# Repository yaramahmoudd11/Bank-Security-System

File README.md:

# 🏦 Bank Smart Security System

An AI-powered smart security system for banks and restricted areas using embedded systems, machine learning, IoT, cloud services, Docker deployment, and real-time mobile monitoring.

---

## 📸 Project Overview

The **Bank Smart Security System** is designed to automate security monitoring in restricted areas such as bank rooms, storage areas, locker rooms, and sensitive access zones.

The system combines:

* A **Raspberry Pi Linux-based unit** for camera processing, face recognition, server communication, GPIO handling, Docker deployment, and cloud integration.
* A **PIC16F877A microcontroller-based unit** for low-level sensor reading, voltage monitoring, relay control, buzzer control, LED indication, and lock control.
* A **Flutter mobile application** for real-time alerts, door control, voltage visualization, outage statistics, and event review.
* **Supabase** for database, storage, and real-time streams.
* **Firebase Cloud Messaging** for push notifications.
* **HuggingFace** for hosting the trained face-recognition classifier/model files.
* **Docker Hub** for Raspberry Pi deployment.

The system detects unauthorized access, after-hours motion intrusion, and power-fault conditions, then sends real-time alerts to the manager through the mobile application.

---

## 🧠 High-Level System Flow

### Face Recognition Flow

```text
Camera → Face Detection → ArcFace Embedding → SVC Classifier
                                                      |
                                                      v
                                              Known? → Log access
                                              Unknown? → Alert App → User decides action
                                                                          |
                                                                          v
                                                              HTTP request to Pi → Alarm / Lock
```

### Sensor and Power Monitoring Flow

```text
PIR Sensor → PIC16F877A → Close door + Light room → Signal Pi → Capture image → Alert App
Voltage Sensor → PIC16F877A → Power statistics → Raspberry Pi → Alert App
```

---

## ✅ Main Features

* Face recognition access control
* Authorized and unauthorized person classification
* PIR motion detection
* Voltage and power-fault monitoring
* Relay-controlled solenoid lock
* Buzzer and LED alarm indicators
* Raspberry Pi camera evidence capture
* Supabase cloud database integration
* Supabase storage for alert images
* Firebase Cloud Messaging notifications
* Real-time mobile alert streaming
* Remote door lock/unlock control
* Live voltage monitoring and visualization
* Power stability percentage
* Outage rate percentage
* Average voltage display
* Backup battery activity indication
* Alert status tracking: `new` and `reviewed`
* Docker deployment on Raspberry Pi
* HuggingFace-hosted face-recognition model files

---

## 🏗️ Final System Architecture

```text
Camera / Sensors
      |
      v
Raspberry Pi Unit + PIC16F877A Unit
      |
      v
Face Recognition + Sensor Processing
      |
      v
Security Decision Logic
      |
      v
Supabase Database + Supabase Storage
      |
      v
Firebase Cloud Messaging
      |
      v
Flutter Mobile Application
      |
      v
Manager Action:
- View alert
- Review alert
- Lock door
- Unlock door
- Ignore alert
```

---

## 🧩 Hardware Components

### Raspberry Pi / Linux-Based Unit

* Raspberry Pi 4
* Camera module
* Python runtime
* OpenCV
* ONNX face recognition models
* Network connection
* GPIO pins for PIR, power outage signal, alarm, and door lock
* Flask HTTP server interface for lock and alert actions
* Docker runtime for containerized deployment

### PIC16F877A Microcontroller Unit

* PIC16F877A microcontroller
* PIR motion sensor
* Voltage sensor module
* 2-channel relay module
* Solenoid lock
* Buzzer
* LEDs
* Logic level converter
* External power supply
* Backup battery switching circuit

---
## 🗂️ Repository Structure

```text
Bank-Security-System/
│
├── README.md
│
├── demo/
│   ├── demo_video_link.txt
│   └── .gitkeep
│
├── docs/
│   ├── diagrams/
│   ├── references/
│   └── schematics/
│
├── face_systems/
│   ├── main.py
│   ├── down.py
│   └── models/
│
├── hardware/
│   ├── pcb/
│   ├── pic_microcontroller/
│   └── wiring_diagrams/
│
├── mobile_app/
│   └── bank_alert_app/
│       ├── lib/
│       ├── android/
│       ├── ios/
│       ├── assets/images/
│       ├── supabase/
│       ├── test/
│       ├── web/
│       ├── windows/
│       ├── linux/
│       ├── macos/
│       ├── pubspec.yaml
│       └── pubspec.lock
│
└── pi/
    ├── Dockerfile
    ├── requirements.txt
    └── run.sh
```

---

## 🧠 Raspberry Pi 4 Unit

The Raspberry Pi acts as the main intelligent processing unit. It handles camera capture, face recognition, GPIO interaction, mobile app commands, Supabase communication, and alert generation.

### Main Tasks

| Task           | Description                                                         |
| -------------- | ------------------------------------------------------------------- |
| Camera loop    | Captures frames continuously using the Pi camera                    |
| Detection loop | Runs face detection and face recognition                            |
| GPIO loop      | Monitors PIR signal and power outage signal from the PIC            |
| Cloud update   | Uploads alerts, images, voltage data, and system states to Supabase |
| HTTP server    | Receives lock/unlock/alarm commands from the mobile app             |

### Flask API Endpoints

| Endpoint            | Action                         |
| ------------------- | ------------------------------ |
| `GET /alert_action` | Trigger alarm for a short time |
| `GET /lock_on`      | Lock the vault/security door   |
| `GET /lock_off`     | Unlock the vault/security door |

---

## ⚙️ GPIO Pin Map — Raspberry Pi 4

| Pin (BCM) | Role                               |
| --------- | ---------------------------------- |
| GPIO 23   | PIR sensor input                   |
| GPIO 24   | Power outage signal input from PIC |
| GPIO 18   | Alarm output                       |
| GPIO 27   | Door lock output                   |

---

## 🔌 PIC16F877A Microcontroller Unit

The PIC16F877A unit handles low-level embedded control. It reads analog and digital inputs, controls relays, activates alarm outputs, monitors voltage, and controls lock-related outputs.

### PIC Pin Mapping

| PIC Pin   | Function                                             |
| --------- | ---------------------------------------------------- |
| RA0 / AN0 | Voltage sensor analog input                          |
| RB1       | PIR motion sensor input / digital security condition |
| RB2       | Additional digital input condition                   |
| RC6 / TX  | UART transmit to Raspberry Pi                        |
| RC7 / RX  | UART receive from Raspberry Pi                       |
| RD0       | Relay / solenoid lock control                        |
| RD1       | Alarm or status output                               |
| RD2       | Low-voltage warning output                           |
| RD3       | Security or motion-related output                    |
| RD4       | Lock/unlock-related output                           |

---

## 🧱 PIC Driver-Based Firmware Structure

The PIC firmware is planned to be organized using a driver-based structure for readability and easier debugging.

## 🧪 Embedded Control Logic

### Voltage Monitoring

The voltage sensor is connected to `RA0/AN0`.

If the measured voltage drops below the selected threshold:

* The low-voltage warning output is activated.
* Backup battery indication can be enabled.
* A power-fault condition is triggered.
* The mobile application displays the outage state through cloud updates.

### PIR Motion Detection

If PIR motion is detected in a restricted area:

* The alarm output is activated.
* The Raspberry Pi captures image evidence.
* An intrusion alert is uploaded to Supabase.
* The mobile application receives a real-time notification.

### Lock Control

The solenoid lock is controlled through a relay.

The lock state can be changed by:

* Local embedded logic
* Raspberry Pi decision logic
* Mobile application remote command

---

## 🤖 Machine Learning Pipeline

The system uses camera-based face recognition to detect whether a person is authorized or unauthorized.

### Pipeline

```text
Camera Frame
      |
      v
YuNet Face Detector
      |
      v
Crop Face
      |
      v
ArcFace Embedding Model
      |
      v
512-D Embedding
      |
      v
SVC Classifier
      |
      v
Name / UNKNOWN
```

### Model on HuggingFace

🤗 **HuggingFace Model:** [Hagar633/face-recognition-svc](https://huggingface.co/Hagar633/face-recognition-svc)

### Model Files

| File                 | Description                          |
| -------------------- | ------------------------------------ |
| `classifier.pkl`     | Trained SVC model saved using joblib |
| `yunet.onnx`         | YuNet face detector                  |
| `w600k_mbf.onnx`     | ArcFace embedding model              |
| `det_500m.onnx`      | Additional detection model           |
| `mobilefacenet.onnx` | Lightweight face model               |

Download all model files from HuggingFace and place them in the models folder before running.

Recommended model folder:

```text
face_systems/models/
```

### Standalone Classifier Example

```python
import joblib

clf = joblib.load("models/classifier.pkl")
prediction = clf.predict(embedding.reshape(1, -1))
```

Confidence threshold:

```text
0.70
```

Predictions below this threshold are treated as `UNKNOWN`.

---

## 🐳 Docker Setup

### Docker Hub Image

```bash
sudo docker pull hagar633/bank_sys2:latest
```

### Build Locally

```bash
cd raspberry_pi/
sudo docker build -t bank_sys .
```

### Run on Raspberry Pi

```bash
sudo ./run.sh
```

The `run.sh` script mounts Raspberry Pi system libraries and Python virtual environment into the container so hardware dependencies such as `picamera2`, `libcamera`, `GPIO`, and `cv2` can work correctly.

Example run command:

```bash
sudo docker run --privileged --network host \
  -v /dev:/dev \
  -v /run/udev:/run/udev:ro \
  -v /usr:/usr:ro \
  -v /lib:/lib:ro \
  -v /home/pi/venv2:/home/pi/venv2:ro \
  -v /home/pi/bank_sys:/app \
  -e PYTHONPATH=/home/pi/venv2/lib/python3.13/site-packages \
  -e LIBCAMERA_IPA_MODULE_PATH=/usr/lib/arm-linux-gnueabihf/libcamera \
  -e SUPABASE_URL="your_supabase_url" \
  -e SUPABASE_KEY="your_supabase_key" \
  --entrypoint /usr/bin/python3.13 \
  bank_sys /app/mergeall3.py
```

### Push to Docker Hub

```bash
sudo docker login
sudo docker tag bank_sys hagar633/bank_sys2:latest
sudo docker push hagar633/bank_sys2:latest
```

---

## 📦 Dependencies

### Python Dependencies

* `opencv-python` — face detection and embedding preprocessing
* `numpy` — numerical operations
* `scikit-learn` / `joblib` — SVC classifier
* `picamera2` — Raspberry Pi camera interface
* `RPi.GPIO` — GPIO control
* `flask` — HTTP API
* `supabase` — cloud database client
* `requests` — HTTP requests
* `python-dotenv` — environment variables

### System Dependencies

* `libcamera`
* Raspberry Pi OS Bookworm 64-bit
* PIC16F877A with custom firmware
* Docker Engine

---

## 📱 Mobile Application Setup

The mobile application is built using Flutter. It displays alerts, receives notifications, shows voltage statistics, and allows the manager to control the door.

### Required Software

* Flutter SDK
* Android Studio or VS Code
* Android Emulator or Android phone
* Firebase project
* Supabase project

### Installation Steps

Go to the mobile app folder:

```bash
cd Bank-Security-System/mobile_app/bank_alert_app
```

Install dependencies:

```bash
flutter pub get
```

Clean previous builds if needed:

```bash
flutter clean
flutter pub get
```

Run the app:

```bash
flutter run
```

---

## ☁️ Supabase Setup

The app connects to Supabase using:

* Supabase project URL
* Supabase anon key
* `alerts` table
* `door_state` table
* `device_tokens` table
* `voltage sensor` table
* `alerts` storage bucket

### Suggested Tables

#### alerts

| Column     | Type      | Description                       |
| ---------- | --------- | --------------------------------- |
| id         | int8      | Alert ID                          |
| category   | text      | `access`, `intrusion`, or `power` |
| message    | text      | Alert message                     |
| image_path | text      | Stored image path                 |
| source_id  | text      | Source unit                       |
| location   | text      | Alert location                    |
| status     | text      | `new` or `reviewed`               |
| created_at | timestamp | Alert creation time               |
| extra_data | jsonb     | Additional event information      |

#### door_state

| Column      | Type      | Description                  |
| ----------- | --------- | ---------------------------- |
| id          | int8      | Fixed row ID, usually 1      |
| is_locked   | bool      | Current lock state           |
| updated_at  | timestamp | Last update time             |
| updated_by  | text      | Source of update             |
| last_reason | text      | Reason for last state change |

#### device_tokens

| Column     | Type      | Description       |
| ---------- | --------- | ----------------- |
| token      | text      | FCM device token  |
| platform   | text      | Device platform   |
| updated_at | timestamp | Last token update |

#### voltage sensor

| Column         | Type      | Description                        |
| -------------- | --------- | ---------------------------------- |
| id             | int8      | Reading ID                         |
| voltage        | float8    | Measured voltage                   |
| adc_value      | int4      | ADC reading                        |
| status         | text      | `NORMAL`, `LOW`, or `POWER_OUTAGE` |
| battery_active | bool      | Backup battery state               |
| created_at     | timestamp | Reading time                       |

---

## 📓 Required Notebook

The final codebase includes:

```text
notebooks/model_finetuning_and_results.ipynb
```

The notebook should document:

* Dataset overview
* Number of enrolled persons
* Number of images per person
* Image preprocessing steps
* Face detection and embedding generation
* Model details
* Recognition threshold
* Similarity score distribution
* Accuracy or evaluation results
* Voltage readings visualization
* Alert category distribution
* Door action statistics
* Inference time analysis
* Power or response-time analysis if measured

---

## ✅ Final Implementation Results

### Access Control

When an unauthorized face is detected:

* The system classifies the person as unauthorized.
* The door remains locked.
* An alert is inserted into the Supabase `alerts` table.
* The captured image is uploaded to Supabase Storage.
* The mobile application displays the alert in the Access tab.
* The manager receives a notification.

### Intrusion Detection

When PIR motion is detected:

* The system triggers an intrusion event.
* Alarm indicators are activated.
* The Raspberry Pi captures image evidence.
* An intrusion alert is sent to the mobile application.
* The manager can review the event and control the door.

### Power Monitoring

When the voltage drops below the defined threshold:

* The PIC detects a low-voltage or outage condition.
* The backup battery indicator is activated.
* A power alert is uploaded to the cloud.
* The mobile app displays the event in the Power tab.
* Live voltage readings are shown in the Voltage tab.

### Mobile Application

The Flutter application provides:

* Splash screen
* Real-time alert list
* Alert details page
* Access alerts tab
* Intrusion alerts tab
* Power alerts tab
* Voltage monitoring tab
* Alert status update
* Door lock/unlock control
* FCM notification support
* Voltage chart
* Power stability percentage
* Outage rate percentage
* Average voltage display
* Battery backup status

---

## 🎬 Demo Scenarios

The following demo scenarios are supported:

1. Authorized user access
2. Unauthorized user detection
3. Motion intrusion detection
4. Power outage detection
5. Remote door lock
6. Remote door unlock
7. Real-time voltage monitoring
8. Mobile notification reception
9. Alert review and status update

---

## 🚀 Running the Full System

### Step 1: Configure Supabase and Firebase

Make sure the following are configured:

* Supabase database tables
* Supabase storage bucket
* Supabase real-time enabled tables
* Firebase Cloud Messaging project
* Flutter Firebase options

### Step 2: Program the PIC

Upload the compiled HEX file to the PIC16F877A.

### Step 3: Start the Raspberry Pi Unit

```bash
cd Bank-Security-System
source venv/bin/activate
python face_systems/main.py
```

### Step 4: Run the Mobile App

```bash
cd mobile_app/bank_alert_app
flutter clean
flutter pub get
flutter run
```

### Step 5: Test the Scenarios

Test the following:

* Face recognition
* Unauthorized access alert
* PIR intrusion alert
* Voltage drop alert
* Door lock command
* Door unlock command
* Notification reception
* Live voltage visualization

---

## 🔐 Security Notes

* Do not publish real Supabase keys, Firebase keys, service account files, or private credentials in a public repository.
* Use `.env` files for local secrets.
* Add secret files to `.gitignore`.
* Use Supabase Row Level Security policies.
* Restrict write access to sensitive tables.
* Validate commands received by the Raspberry Pi before controlling the lock.

Recommended `.gitignore` entries:

```text
.env
*.env
serviceAccountKey.json
firebase-service-account.json
*firebase-adminsdk*.json
google-services.json
GoogleService-Info.plist
node_modules/
__pycache__/
venv/
build/
.dart_tool/
*.log
```

---

## 📚 Documentation

Project documentation is stored in:

```text
docs/
```

It includes:

* System architecture diagram
* Input/output diagram
* Electrical schematic
* PCB documentation
* Reference papers
* Screenshots
* Test results

---

## 🔗 Links

* 🐳 Docker Hub: [hagar633/bank_sys](https://hub.docker.com/r/hagar633/bank_sys2)
* 🤗 HuggingFace Model: [Hagar633/face-recognition-svc](https://huggingface.co/Hagar633/face-recognition-svc)
* 💻 GitHub: [yaramahmoudd11/Bank-Security-System](https://github.com/yaramahmoudd11/Bank-Security-System)

---

## 👥 Authors

* Yara Mahmoud
* Filopater Emad
* Hagar Alsherbiny

---

## 📄 License

This project is developed for educational and academic purposes.

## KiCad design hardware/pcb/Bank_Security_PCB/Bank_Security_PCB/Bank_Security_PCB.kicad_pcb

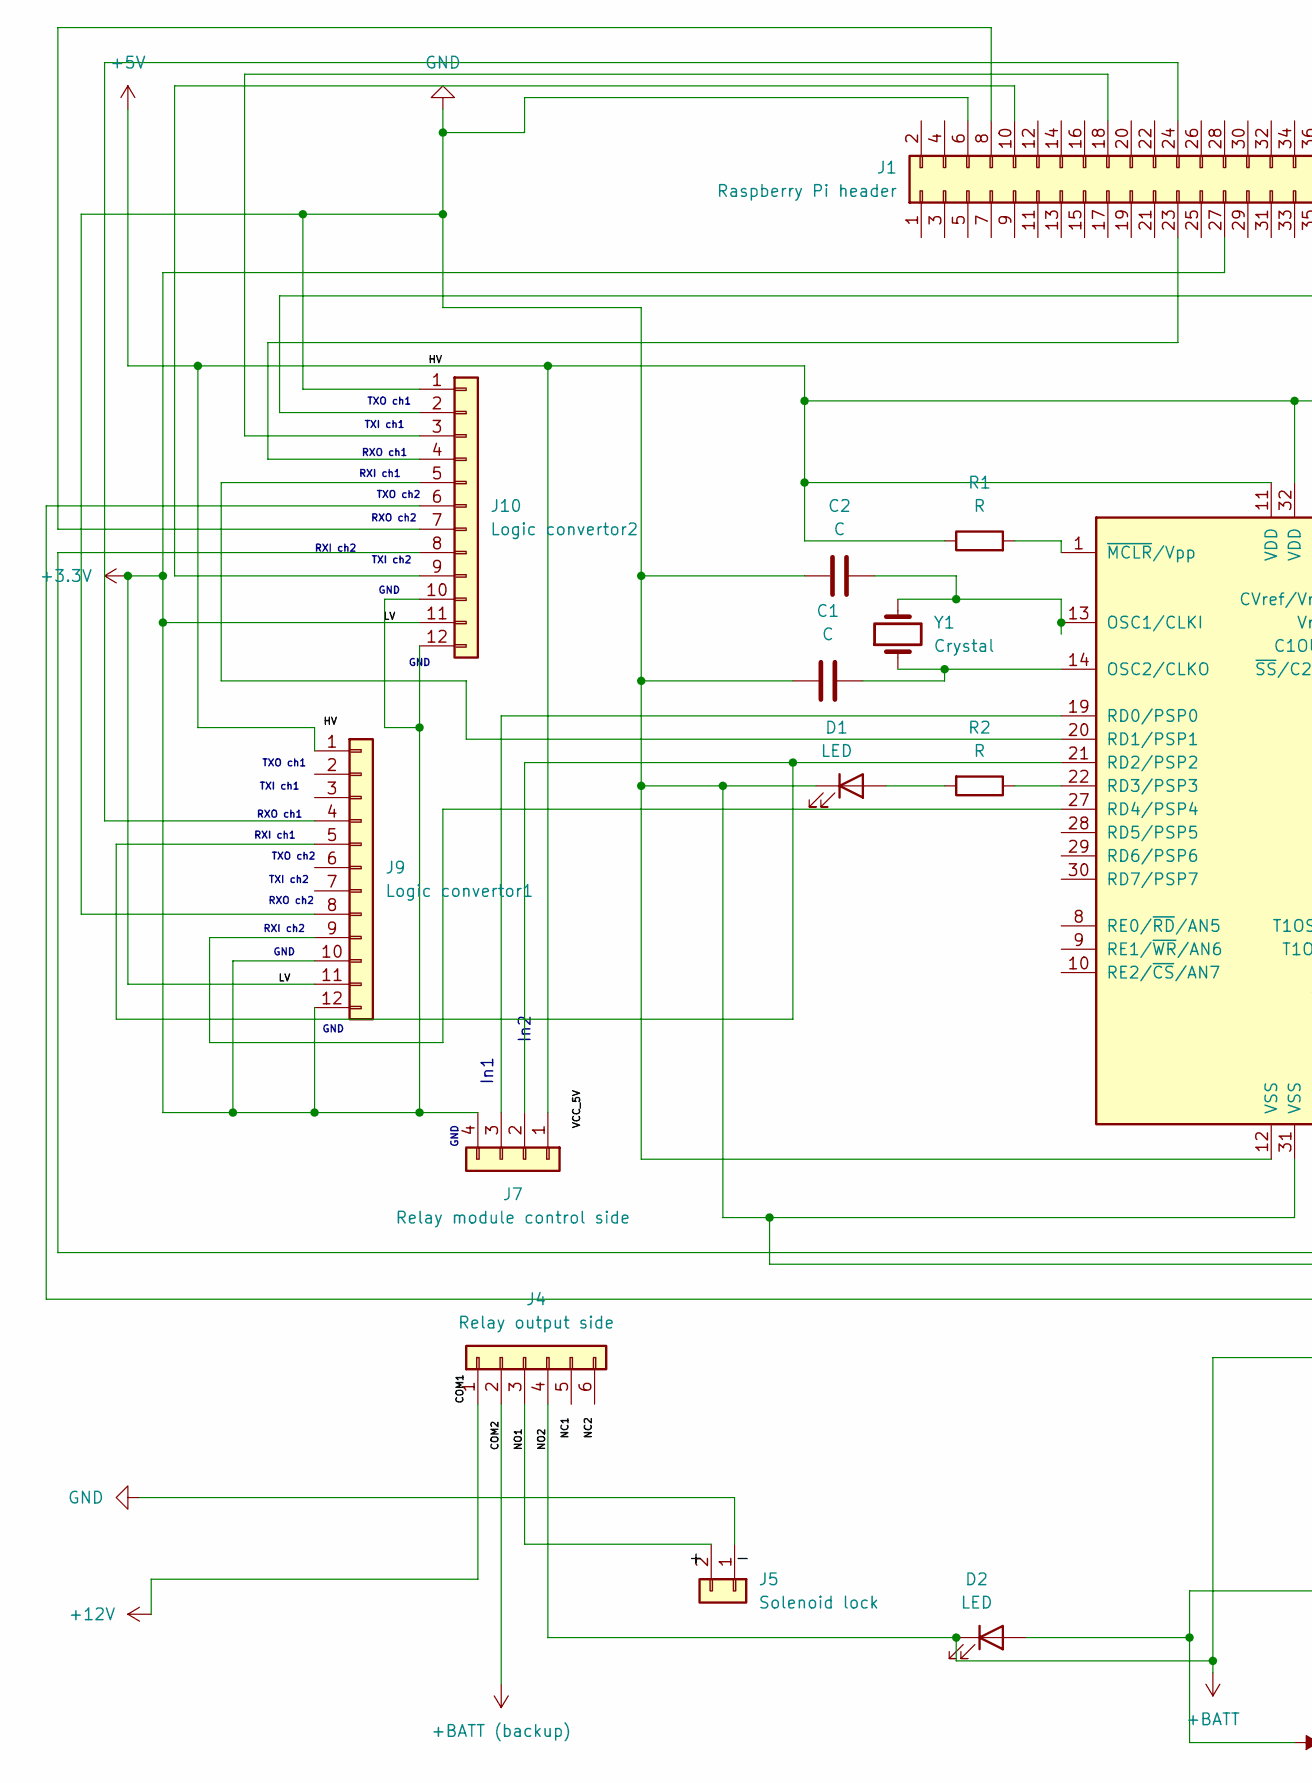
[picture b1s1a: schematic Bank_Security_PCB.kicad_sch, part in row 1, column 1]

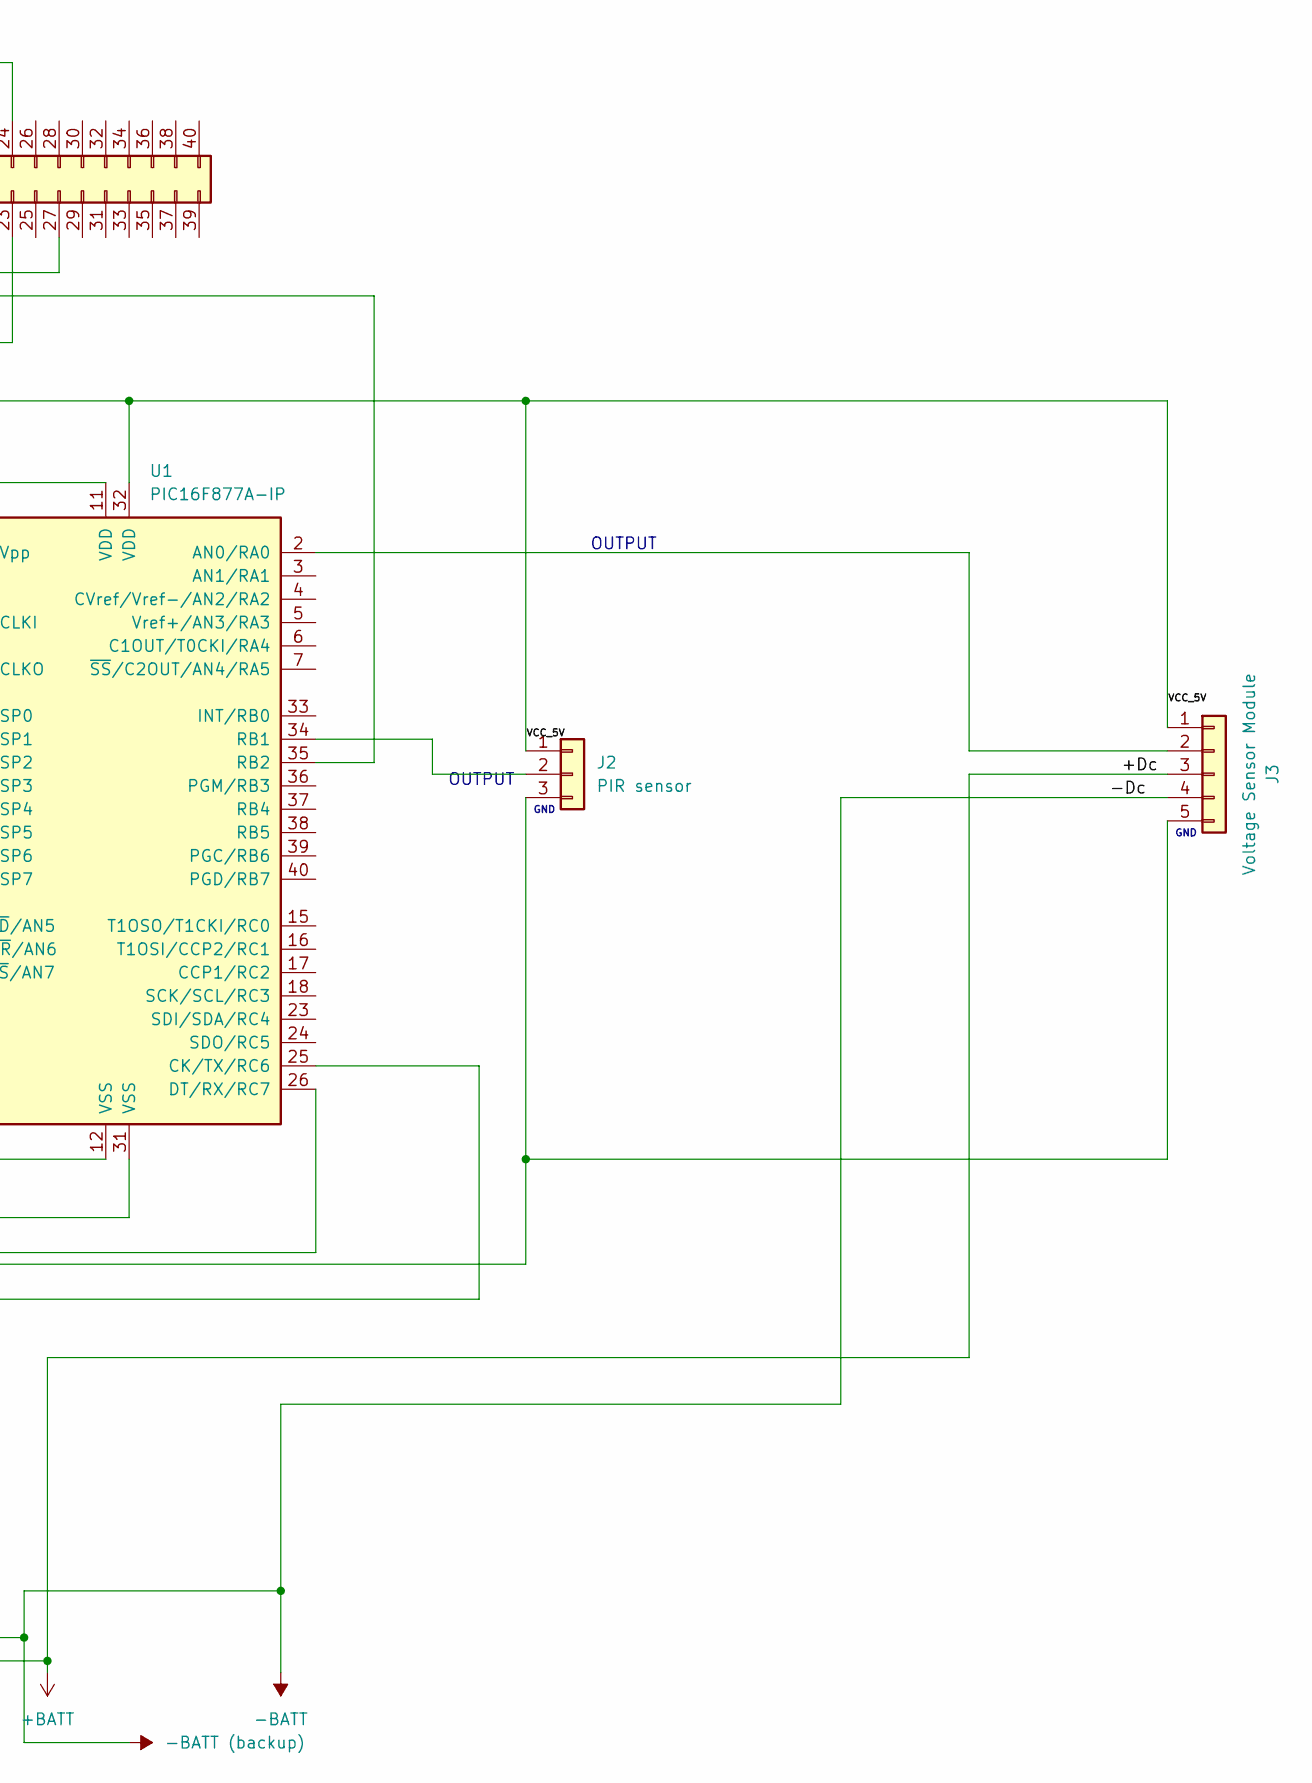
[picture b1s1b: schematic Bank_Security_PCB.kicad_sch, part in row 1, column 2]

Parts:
C1, C2: C; C_Disc_D5.0mm_W2.5mm_P5.00mm
D1, D2: LED; LED_D5.0mm
J1: Raspberry Pi header; PinHeader_2x20_P2.54mm_Vertical
J2: PIR sensor; PinHeader_1x03_P2.54mm_Vertical
J3: Voltage Sensor Module; PinHeader_1x05_P2.54mm_Vertical
J4: Relay output side; PinHeader_1x06_P2.54mm_Vertical
J5: Solenoid lock; TerminalBlock_CUI_TB007-508-02_1x02_P5.08mm_Horizontal
J7: Relay module control side; PinHeader_1x04_P2.54mm_Vertical
J9: Logic convertor1; PinHeader_1x12_P2.54mm_Vertical
J10: Logic convertor2; PinHeader_1x12_P2.54mm_Vertical
R1, R2: R; R_Axial_DIN0207_L6.3mm_D2.5mm_P7.62mm_Horizontal
U1: PIC16F877A-IP; DIP-40_W15.24mm
Y1: Crystal; Crystal_HC49-U_Vertical

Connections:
+3.3V: J1.27, J7.4, J9.10, J9.11, J9.12, J10.10, J10.11, J10.12
+5V: J2.1, J3.1, J7.1, J9.1, R1.1, U1.11 (VDD), U1.32 (VDD)
+12V: J4.1
+BATT: D2.1 (K), J3.3, J4.4
+BATT (backup): J4.2
-BATT: D2.2 (A), J3.4
/NO1: J4.3, J5.2
GND: C1.1, C2.2, D1.1 (K), J1.6, J2.3, J3.5, J5.1, J9.8, J10.1, U1.12 (VSS), U1.31 (VSS)
unnamed: D1.2 (A), R2.2
unnamed: J1.8, J10.7
unnamed: J1.10, J10.9
unnamed: J1.18, J10.3
unnamed: J1.23, J10.4
unnamed: J1.24, J9.4
unnamed: J2.2, U1.34 (RB1)
unnamed: J3.2, U1.2 (AN0/RA0)
unnamed: J7.2, J9.5, U1.21 (RD2/PSP2)
unnamed: J7.3, U1.19 (RD0/PSP0)
unnamed: J9.9, U1.27 (RD4/PSP4)
unnamed: J10.2, U1.35 (RB2)
unnamed: J10.5, U1.20 (RD1/PSP1)
unnamed: J10.6, U1.25 (CK/TX/RC6)
unnamed: J10.8, U1.26 (DT/RX/RC7)
unnamed: C2.1, U1.13 (OSC1/CLKI), Y1.2
unnamed: C1.2, U1.14 (OSC2/CLKO), Y1.1
unnamed: R2.1, U1.22 (RD3/PSP3)
unnamed: R1.2, U1.1 (~MCLR/Vpp)

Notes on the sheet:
RXI ch2
TXI ch2
In2
TXO ch2
TXO ch1
GND
OUTPUT
RXI ch1
TXI ch1
RXO ch1
RXO ch2
In1

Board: 2 copper layers, 16 parts (0 on the bottom side), 25 nets, no tracks yet.

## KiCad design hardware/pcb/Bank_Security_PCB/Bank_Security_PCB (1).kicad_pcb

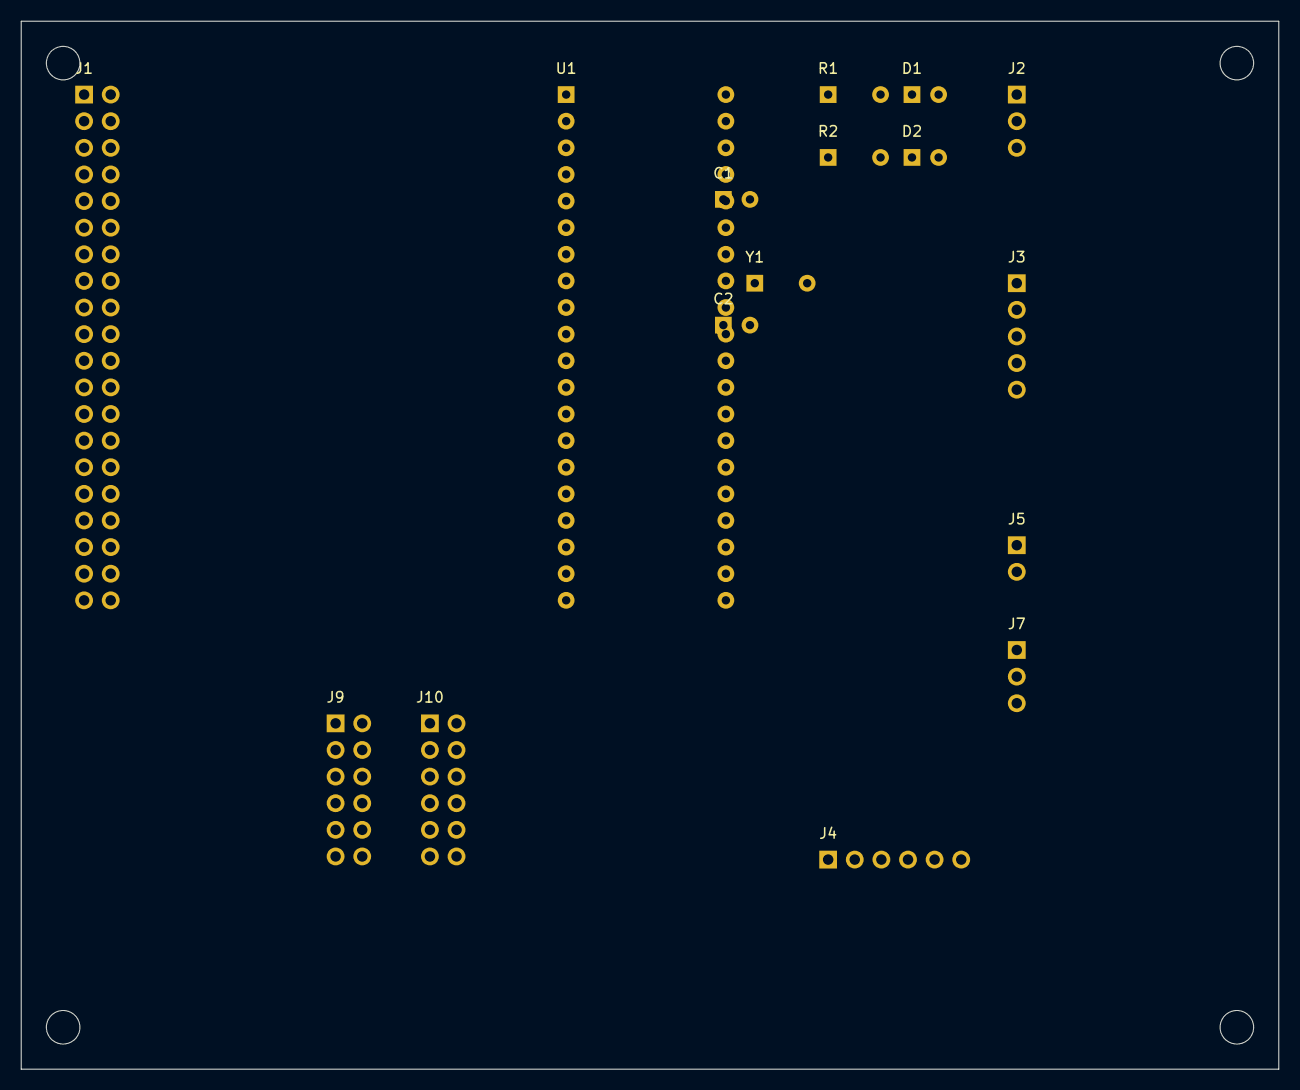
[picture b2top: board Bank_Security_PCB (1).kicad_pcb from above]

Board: 2 copper layers, 120.0 x 100.0 mm, 20 parts (0 on the bottom side), 13 nets, no tracks yet.

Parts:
C1, C2: C_100nF
D1, D2: LED
J1: RPi_Header_40
J2: PIR_Sensor
J3: VoltageSensor
J4: RelayOut
J5: Solenoid
J7: RelayCtrl
J9: LogicConv1
J10: LogicConv2
MH: MountingHole
MH#2, MH#3, MH#4: MountingHole
R1, R2: R_330ohm
U1: PIC16F877A-IP
Y1: Crystal_HC49S

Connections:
+3V3: J1.1, J1.17, J9.1, J10.1
+12V: J3.1, J9.2, J10.2
/LED1: D1.1, R1.2
/LED2: D2.1, R2.2
/OSC1: U1.13, Y1.1
/OSC2: U1.14, Y1.2
/RC3_SCL: J1.28, U1.18
/RC4_SDA: J1.27, U1.23
/RC6_TX: J1.8, J9.5, J9.8, J10.5, J10.8, U1.25
/RC7_RX: J1.10, J9.6, J9.7, J10.6, J10.7, U1.26
/SOLENOID: J4.3, J4.4, J5.1
GND: C1.2, C2.2, D1.2, D2.2, J1.6, J1.14, J1.20, J1.25, J1.34, J1.39, J2.2, J3.2, J4.2, J5.2, J7.2, J9.3, J9.4, J9.11, J9.12, J10.3, J10.4, J10.11, J10.12, U1.12, U1.31
VDD: C1.1, C2.1, J1.2, J1.4, J4.1, J7.1, R1.1, R2.1, U1.11, U1.32

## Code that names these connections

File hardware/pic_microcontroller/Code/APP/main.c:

/******************************************************************************
* @file main.c
* @brief PIC16F877A Security + Voltage Control - Driver Format
* @target PIC16F877A
******************************************************************************/

#include "../MCAL/GPIO/GPIO_interface.h"
#include "../MCAL/ADC/ADC_Interface.h"
#include "../MCAL/UART/UART_Interface.h"

#include "../HAL/LED/LED_interface.h"
#include "../HAL/SWITCH/SWITCH_interface.h"

#include "../SERVICES/STD_TYPES.h"

/* ========================== PIN MAPPING ================================== */

/* ADC */
#define VOLTAGE_ADC_CHANNEL          ADC_CHANNEL_0     /* RA0 / AN0 */

/*
 * ADC Reference = 5V
 * 1V => (1 / 5) * 1023 = 204.6
 * ADC values 0..204 are below 1V
 */
#define VOLTAGE_1V_THRESHOLD_ADC     205U

/* Inputs */
#define PIR_INPUT_PORT               GPIO_PORTB
#define PIR_INPUT_PIN                GPIO_PIN1         /* RB1 */

#define LOCK_INPUT_PORT              GPIO_PORTB
#define LOCK_INPUT_PIN               GPIO_PIN2         /* RB2 */

#define EXTRA_INPUT_PORT             GPIO_PORTD
#define EXTRA_INPUT_PIN              GPIO_PIN4         /* RD4 */

#define VOLTAGE_INPUT_PORT           GPIO_PORTA
#define VOLTAGE_INPUT_PIN            GPIO_PIN0         /* RA0 / AN0 */

/* Outputs */
#define LOCK_OUTPUT_PORT             GPIO_PORTD
#define LOCK_OUTPUT_PIN              GPIO_PIN0         /* RD0 */

#define ALARM_OUTPUT_PORT            GPIO_PORTD
#define ALARM_OUTPUT_PIN             GPIO_PIN1         /* RD1 */

#define VOLTAGE_OUTPUT_PORT          GPIO_PORTD
#define VOLTAGE_OUTPUT_PIN           GPIO_PIN2         /* RD2 */

#define PIR_LED_PORT                 GPIO_PORTD
#define PIR_LED_PIN                  GPIO_PIN3         /* RD3 */

/* UART pins */
#define UART_TX_PORT                 GPIO_PORTC
#define UART_TX_PIN                  GPIO_PIN6         /* RC6 / TX */

#define UART_RX_PORT                 GPIO_PORTC
#define UART_RX_PIN                  GPIO_PIN7         /* RC7 / RX */

/* ========================== GLOBAL VARIABLES ============================= */

static u8  rb1_state = 0;
static u8  rb2_state = 0;
static u8  rd4_state = 0;
static u16 adc_value = 0;

/* ========================== FUNCTION PROTOTYPES =========================== */

static void System_Init(void);
static void Read_Inputs(void);
static void Apply_Output_Logic(void);
static void Send_ADC_UART(void);

/* ========================== MAIN ========================================= */

void main(void)
{
    System_Init();

    while(1)
    {
        Read_Inputs();
        Apply_Output_Logic();
        Send_ADC_UART();

        Delay_ms(500);
    }
}

/* ========================== SYSTEM INIT ================================== */

static void System_Init(void)
{
    /* ================= Inputs ================= */

    SWITCH_Init(PIR_INPUT_PORT, PIR_INPUT_PIN);       /* RB1 input */
    SWITCH_Init(LOCK_INPUT_PORT, LOCK_INPUT_PIN);     /* RB2 input */
    SWITCH_Init(EXTRA_INPUT_PORT, EXTRA_INPUT_PIN);   /* RD4 input */

    GPIO_SetPinDirection(VOLTAGE_INPUT_PORT,
                         VOLTAGE_INPUT_PIN,
                         GPIO_INPUT);                 /* RA0 / AN0 input */

    /* ================= Outputs ================ */

    GPIO_SetPinDirection(LOCK_OUTPUT_PORT,
                         LOCK_OUTPUT_PIN,
                         GPIO_OUTPUT);                /* RD0 output */

    GPIO_SetPinDirection(ALARM_OUTPUT_PORT,
                         ALARM_OUTPUT_PIN,
                         GPIO_OUTPUT);                /* RD1 output */

    GPIO_SetPinDirection(VOLTAGE_OUTPUT_PORT,
                         VOLTAGE_OUTPUT_PIN,
                         GPIO_OUTPUT);                /* RD2 output */

    LED_Init(PIR_LED_PORT, PIR_LED_PIN);              /* RD3 LED only */

    /* ================= UART Pins =============== */

    GPIO_SetPinDirection(UART_TX_PORT,
                         UART_TX_PIN,
                         GPIO_OUTPUT);                /* RC6 / TX */

    GPIO_SetPinDirection(UART_RX_PORT,
                         UART_RX_PIN,
                         GPIO_INPUT);                 /* RC7 / RX */

    /* ================= Initial States ========== */

    GPIO_SetPinValue(LOCK_OUTPUT_PORT,
                     LOCK_OUTPUT_PIN,
                     GPIO_LOW);                       /* RD0 LOW */

    GPIO_SetPinValue(ALARM_OUTPUT_PORT,
                     ALARM_OUTPUT_PIN,
                     GPIO_LOW);                       /* RD1 LOW */

    GPIO_SetPinValue(VOLTAGE_OUTPUT_PORT,
                     VOLTAGE_OUTPUT_PIN,
                     GPIO_LOW);                       /* RD2 LOW */

    LED_Off(PIR_LED_PORT, PIR_LED_PIN);               /* RD3 LOW */

    /* ================= Drivers Init ============ */

    ADC_Init();
    UART_Init();
}

/* ========================== READ INPUTS ================================== */

static void Read_Inputs(void)
{
    rb1_state = SWITCH_GetState(PIR_INPUT_PORT, PIR_INPUT_PIN);
    rb2_state = SWITCH_GetState(LOCK_INPUT_PORT, LOCK_INPUT_PIN);
    rd4_state = SWITCH_GetState(EXTRA_INPUT_PORT, EXTRA_INPUT_PIN);

    adc_value = ADC_ReadChannel(VOLTAGE_ADC_CHANNEL);
}

/* ========================== APPLY LOGIC ================================== */

static void Apply_Output_Logic(void)
{
    /*
     * Same original logic:
     *
     * If RB1 = 1:
     *      RD3 = HIGH
     *      RD0 = HIGH
     *      RD1 = HIGH
     *
     * Else if RB2 = 1 OR RD4 = 1:
     *      RD3 = LOW
     *      RD0 = HIGH
     *      RD1 = LOW
     *
     * Else:
     *      RD3 = LOW
     *      RD0 = LOW
     *      RD1 = LOW
     */

    if(rb1_state == GPIO_HIGH)
    {
        LED_On(PIR_LED_PORT, PIR_LED_PIN);                         /* RD3 */

        GPIO_SetPinValue(LOCK_OUTPUT_PORT,
                         LOCK_OUTPUT_PIN,
                         GPIO_HIGH);                               /* RD0 */

        GPIO_SetPinValue(ALARM_OUTPUT_PORT,
                         ALARM_OUTPUT_PIN,
                         GPIO_HIGH);                               /* RD1 */
    }
    else if((rb2_state == GPIO_HIGH) || (rd4_state == GPIO_HIGH))
    {
        LED_Off(PIR_LED_PORT, PIR_LED_PIN);                        /* RD3 */

        GPIO_SetPinValue(LOCK_OUTPUT_PORT,
                         LOCK_OUTPUT_PIN,
                         GPIO_HIGH);                               /* RD0 */

        GPIO_SetPinValue(ALARM_OUTPUT_PORT,
                         ALARM_OUTPUT_PIN,
                         GPIO_LOW);                                /* RD1 */
    }
    else
    {
        LED_Off(PIR_LED_PORT, PIR_LED_PIN);                        /* RD3 */

        GPIO_SetPinValue(LOCK_OUTPUT_PORT,
                         LOCK_OUTPUT_PIN,
                         GPIO_LOW);                                /* RD0 */

        GPIO_SetPinValue(ALARM_OUTPUT_PORT,
                         ALARM_OUTPUT_PIN,
                         GPIO_LOW);                                /* RD1 */
    }

    /*
     * Voltage logic:
     * ADC < 205  => RA0 voltage < 1V  => RD2 HIGH
     * ADC >= 205 => RA0 voltage >= 1V => RD2 LOW
     */

    if(adc_value < VOLTAGE_1V_THRESHOLD_ADC)
    {
        GPIO_SetPinValue(VOLTAGE_OUTPUT_PORT,
                         VOLTAGE_OUTPUT_PIN,
                         GPIO_HIGH);                               /* RD2 */
    }
    else
    {
        GPIO_SetPinValue(VOLTAGE_OUTPUT_PORT,
                         VOLTAGE_OUTPUT_PIN,
                         GPIO_LOW);                                /* RD2 */
    }
}

/* ========================== UART SEND ==================================== */

static void Send_ADC_UART(void)
{
    /*
     * Send ADC value as 2 binary bytes:
     * First byte  = high byte
     * Second byte = low byte
     */

    UART_SendByte((u8)(adc_value >> 8));
    UART_SendByte((u8)(adc_value & 0xFF));
}

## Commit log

2026-05-15 Initial project structure
2026-05-15 Add Flutter mobile app
2026-05-15 Add face embedding system code
2026-05-15 Add schematics diagrams and reference papers
2026-05-15 Revise README for clarity and completeness
    Updated README to enhance project details and structure.
2026-05-15 Add mobile app
2026-05-16 Remove old structure
2026-05-16 Add pi folder and README
2026-05-16 Update README.md
    Removed team section from the README.
2026-05-16 Add face recognition system
2026-05-16 Add model ipngb notebook
2026-05-16 Update model ipngb notebook
2026-05-16 Change Docker Hub image name to bank_sys2
    Updated Docker Hub image references from 'bank_sys' to 'bank_sys2'.
2026-05-16 Update PIC drivers and add UART ADC transmission
2026-05-17 Refactor main.c for clarity and functionality
    Refactor main.c for improved clarity and functionality.
2026-05-18 Update PIC microcontroller code
2026-05-24 Add PCB design and manufacturing files
